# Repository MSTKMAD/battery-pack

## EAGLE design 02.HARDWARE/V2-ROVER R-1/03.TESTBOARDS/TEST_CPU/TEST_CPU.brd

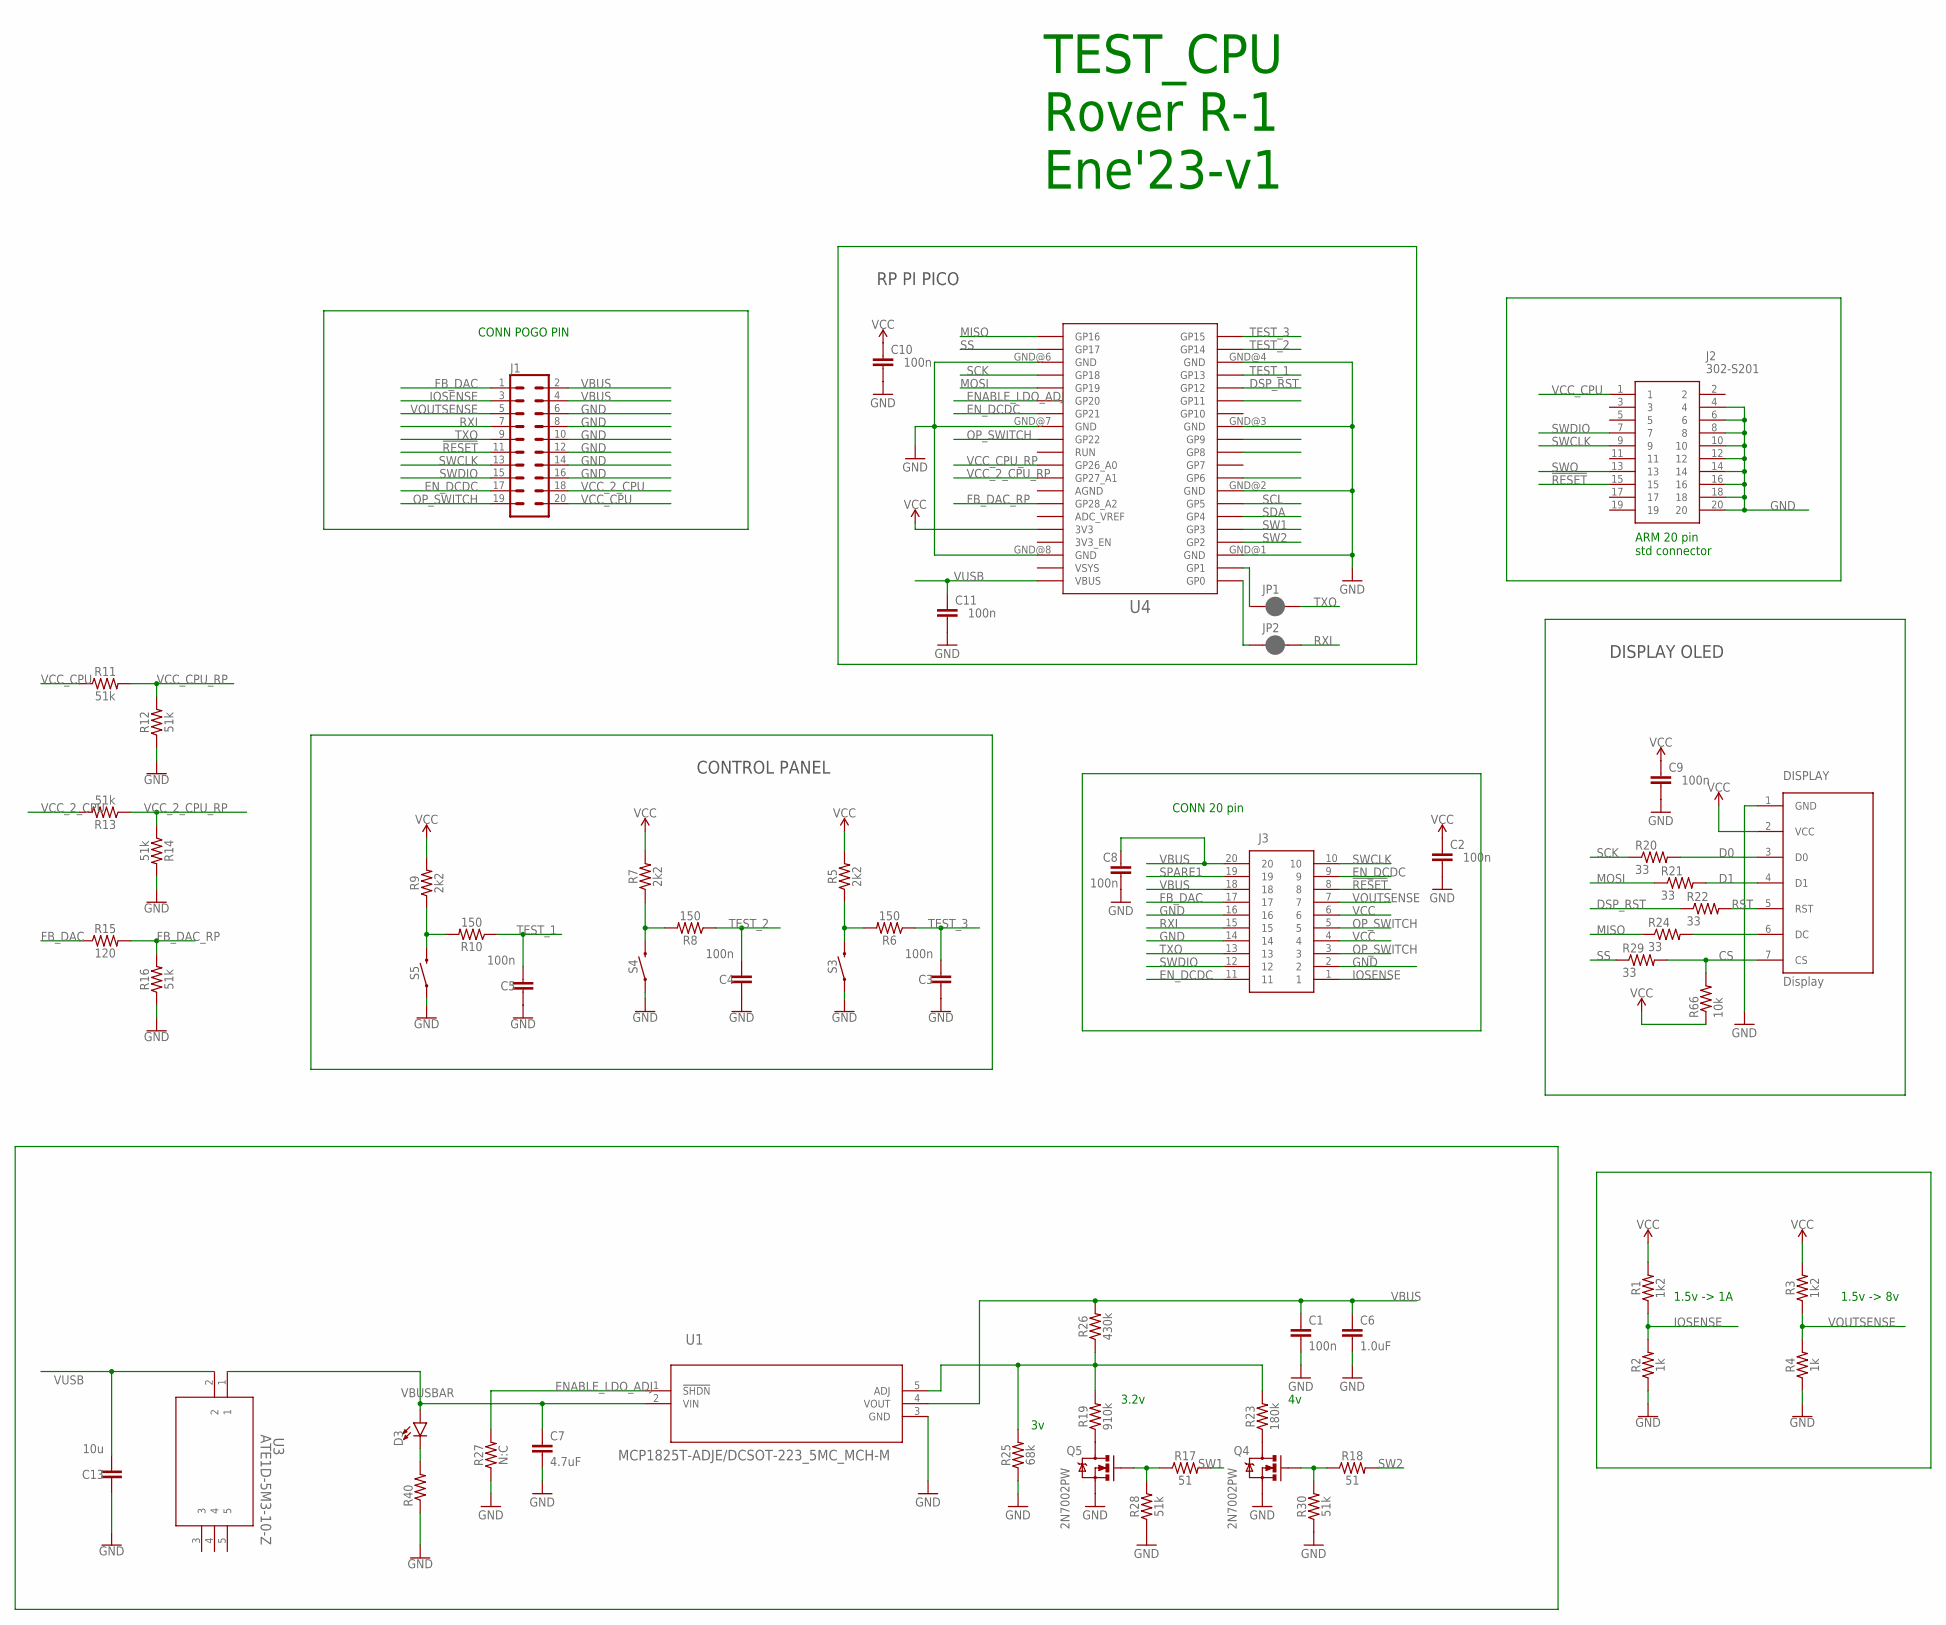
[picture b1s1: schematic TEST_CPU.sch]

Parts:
C1, C2, C3, C4, C5, C8, C9, C10, C11: 100n; 0805
C6: 1.0uF; 0805
C7: 4.7uF; 0805
C13: 10u; 0805
D3: LED3MM; LED_3MM
DISPLAY: Display; OLED_LCD
J1: CONN_10X2; 2X10
J2: 302-S201; SHDR20W66P254_2X10_3300X905X90
J3: DF40C-20DP-0.4V_51_; DF40C-20DPA
JP1, JP2: JUMPER-SMT_2_NC_PASTE_SILK; SMT-JUMPER_2_NC_PASTE_SILK
Q4, Q5: 2N7002PW; SOT323
R1, R3: 1k2; 0805
R2, R4: 1k; 0805
R5, R7, R9: 2k2; 0805
R6, R8, R10: 150; 0805
R11, R12, R13, R14, R16, R28, R30: 51k; 0805
R15: 120; 0805
R17, R18: 51; 0805
R19: 910k; 0805
R20, R21, R22, R24, R29: 33; 0805
R23: 180k; 0805
R25: 68k; 0805
R26: 430k; 0805
R27: N:C; 0805
R40: 360; 0805
R66: 10k; 0805
S3, S4, S5: MOMENTARY-SWITCH-SPST-SMD-5.2MM; TACTILE_SWITCH_SMD_5.2MM
U1: MCP1825T-ADJE/DCSOT-223_5MC_MCH-M; SOT-223_5MC_MCH-M
U3: ATE1D-5M3-10-Z; SPDT05_ATE1D_9P5X8_NDC
U4: RPI_PICO_IG-TH; RPI_PICO_TH

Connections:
!RESET: J1.11, J2.15, J3.8
CS: DISPLAY.7 (CS), R29.2, R66.2
D0: DISPLAY.3 (D0), R20.2
D1: DISPLAY.4 (D1), R21.2
DSP_RST: R22.1, U4.GP12
ENABLE_LDO_ADJ: R27.2, U1.1 (!SHDN), U4.GP20
EN_DCDC: J1.17, J3.9, J3.11, U4.GP21
FB_DAC: J1.1, J3.17, R15.1
FB_DAC_RP: R15.2, R16.2, U4.GP28_A2
GND: C1.2, C2.2, C3.1, C4.1, C5.1, C6.2, C7.2, C8.2, C9.2, C10.2, C11.2, C13.1, DISPLAY.1 (GND), J1.6, J1.8, J1.10, J1.12, J1.14, J1.16, J2.4, J2.6, J2.8, J2.10, J2.12, J2.14, J2.16, J2.18, J2.20, J3.2, J3.14, J3.16, Q4.2 (S), Q5.2 (S), R2.1, R4.1, R12.1, R14.2, R16.1, R25.1, R27.1, R28.1, R30.1, R40.1, S3.1, S4.1, S5.1, U1.3 (GND), U4.GND@1 (GND), U4.GND@2 (GND), U4.GND@3 (GND), U4.GND@4 (GND), U4.GND@6 (GND), U4.GND@7 (GND), U4.GND@8 (GND)
IOSENSE: J1.3, J3.1, R1.1, R2.2
MISO: R24.1, U4.GP16
MOSI: R21.1, U4.GP19
unnamed: R5.1, R6.2, S3.3 (2)
unnamed: R7.1, R8.2, S4.3 (2)
unnamed: JP1.1, U4.GP1
unnamed: R9.1, R10.2, S5.3 (2)
unnamed: JP2.1, U4.GP0
unnamed: DISPLAY.6 (DC), R24.2
unnamed: R19.2, R23.2, R25.2, R26.1, U1.5 (ADJ)
unnamed: Q5.1 (G), R17.1, R28.2
unnamed: D3.K (C), R40.2
unnamed: Q5.3 (D), R19.1
unnamed: Q4.1 (G), R18.1, R30.2
unnamed: Q4.3 (D), R23.1
OP_SWITCH: J1.19, J3.3, J3.5, U4.GP22
RST: DISPLAY.5 (RST), R22.2
RXI: J1.7, J3.15, JP2.2
SCK: R20.1, U4.GP18
SCL: U4.GP5
SDA: U4.GP4
SPARE1: J3.19
SS: R29.1, U4.GP17
SW1: R17.2, U4.GP3
SW2: R18.2, U4.GP2
SWCLK: J1.13, J2.9, J3.10
SWDIO: J1.15, J2.7, J3.12
SWO: J2.13
TEST_1: C5.2, R10.1, U4.GP13
TEST_2: C4.2, R8.1, U4.GP14
TEST_3: C3.2, R6.1, U4.GP15
TXO: J1.9, J3.13, JP1.2
VBUS: C1.1, C6.1, C8.1, J1.2, J1.4, J3.18, J3.20, R26.2, U1.4 (VOUT)
VBUSBAR: C7.1, D3.A, U1.2 (VIN), U3.1
VCC: C2.1, C9.1, C10.1, DISPLAY.2 (VCC), J3.4, J3.6, R1.2, R3.2, R5.2, R7.2, R9.2, R66.1, U4.3V3
VCC_2_CPU: J1.18, R13.2
VCC_2_CPU_RP: R13.1, R14.1, U4.GP27_A1
VCC_CPU: J1.20, J2.1, R11.1
VCC_CPU_RP: R11.2, R12.2, U4.GP26_A0
VOUTSENSE: J1.5, J3.7, R3.1, R4.2
VUSB: C11.1, C13.2, U3.2, U4.VBUS

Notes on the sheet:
TEST_CPU Rover R-1 Ene'23-v1
CONTROL PANEL
DISPLAY OLED
RP PI PICO
ARM 20 pin std connector
CONN 20 pin
CONN POGO PIN
1.5v -> 1A
1.5v -> 8v
3.2v

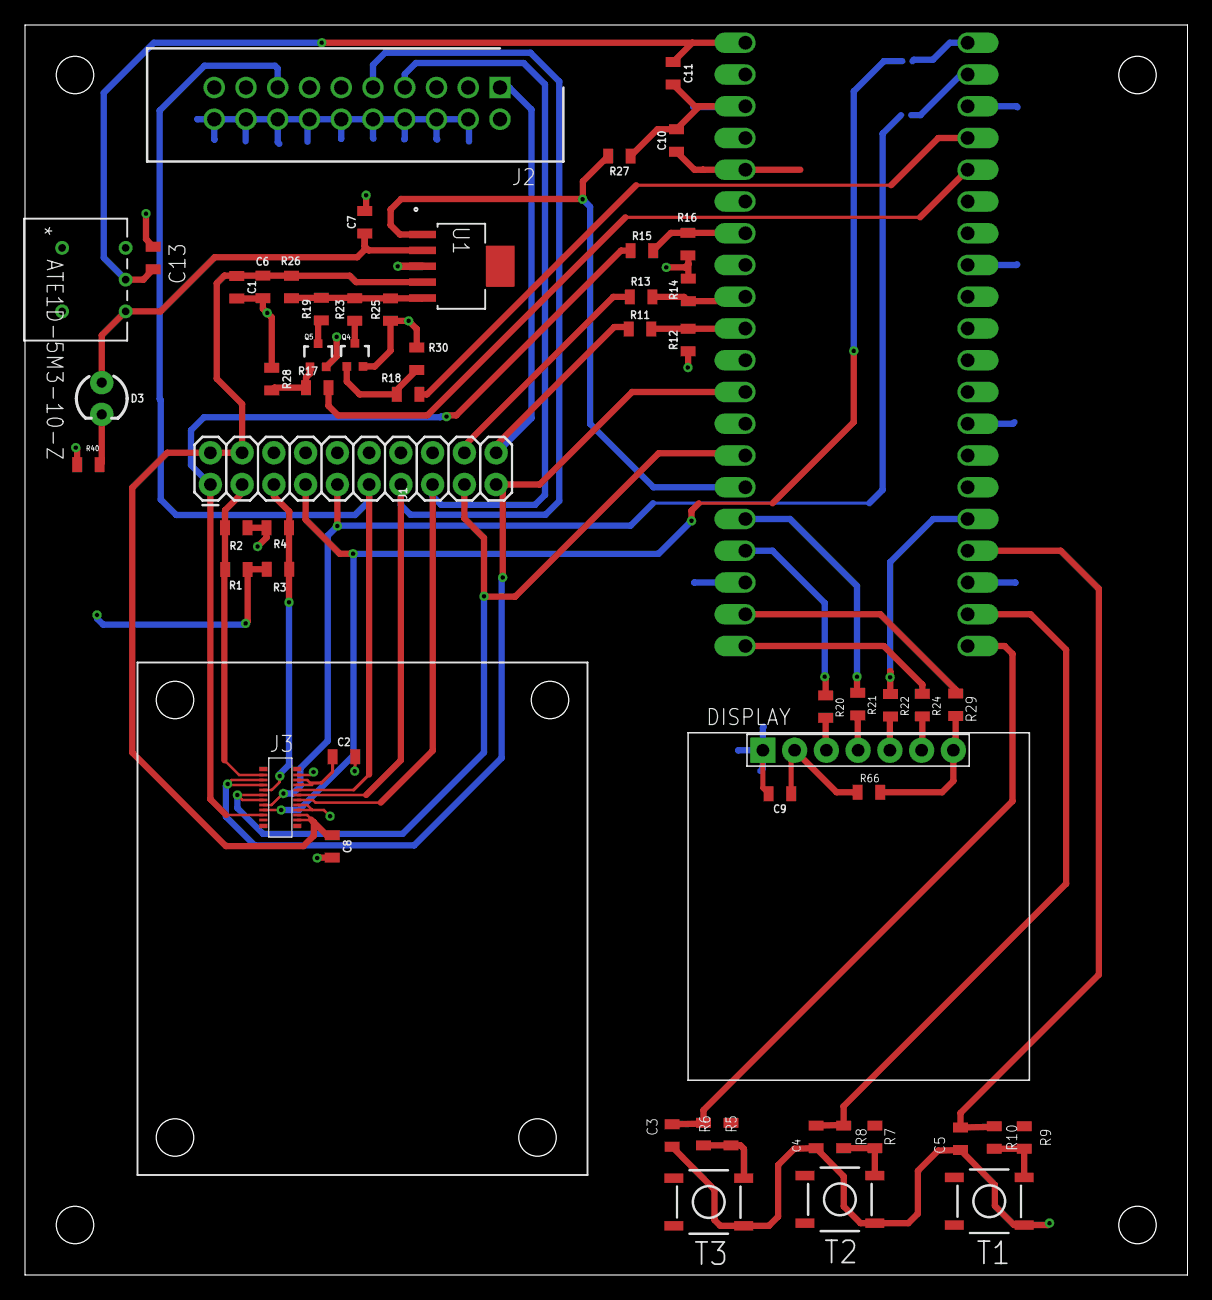
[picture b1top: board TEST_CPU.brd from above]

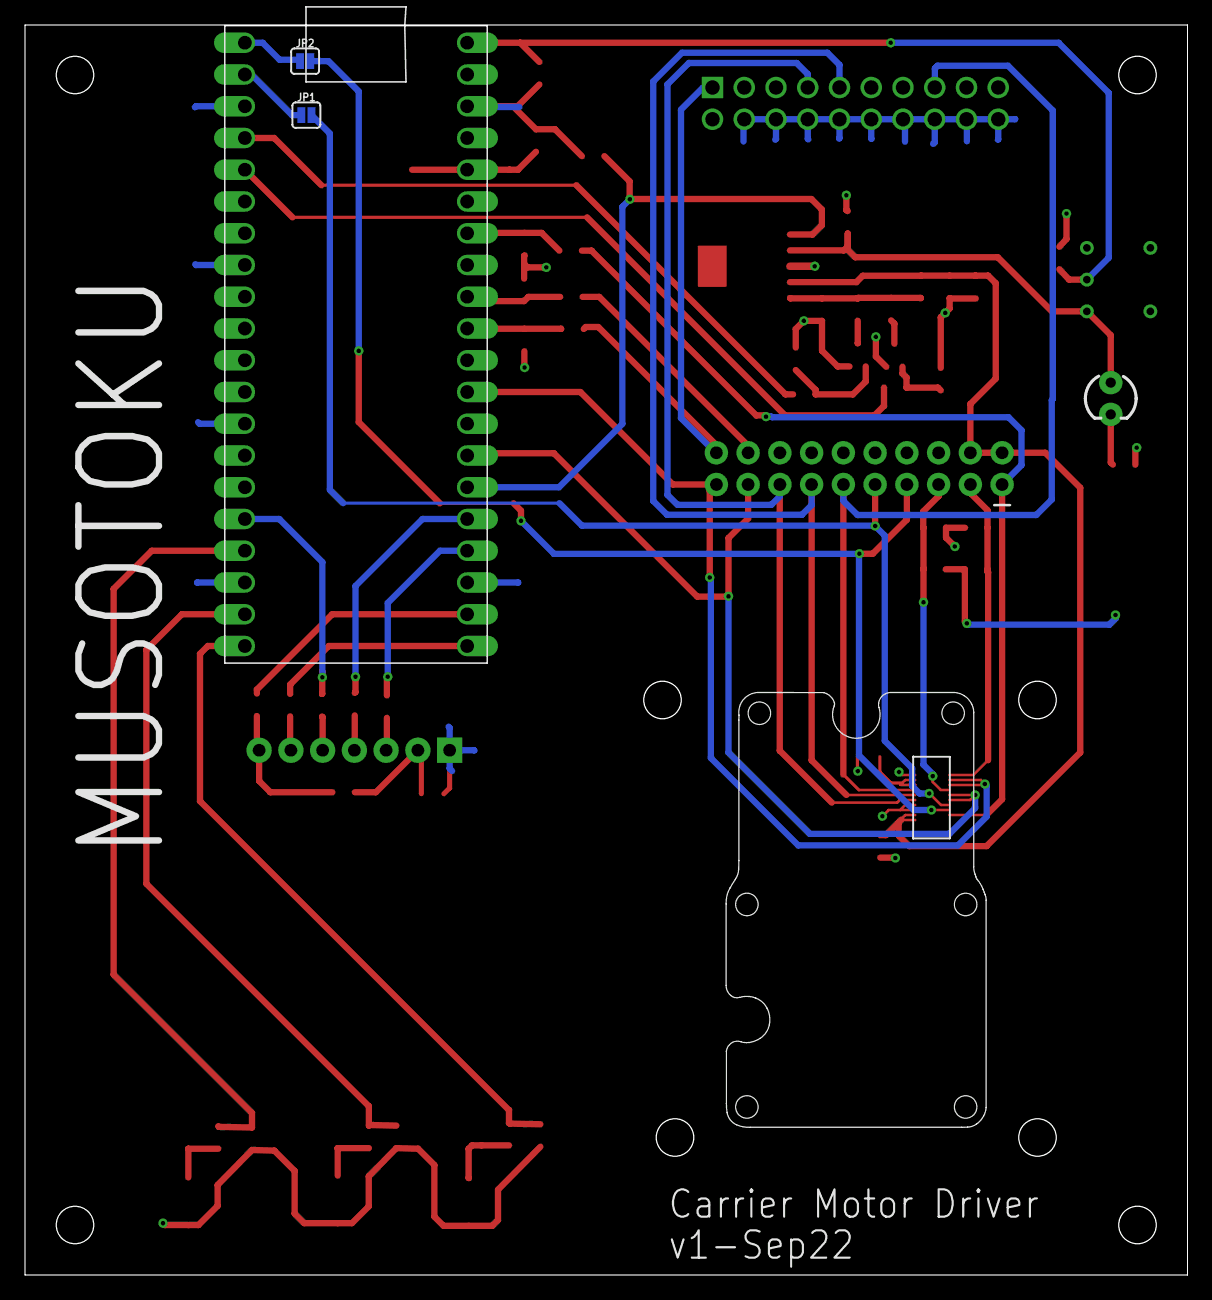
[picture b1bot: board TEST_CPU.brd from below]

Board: 2 copper layers, 93.0 x 100.0 mm, 59 parts (3 on the bottom side), 47 nets.

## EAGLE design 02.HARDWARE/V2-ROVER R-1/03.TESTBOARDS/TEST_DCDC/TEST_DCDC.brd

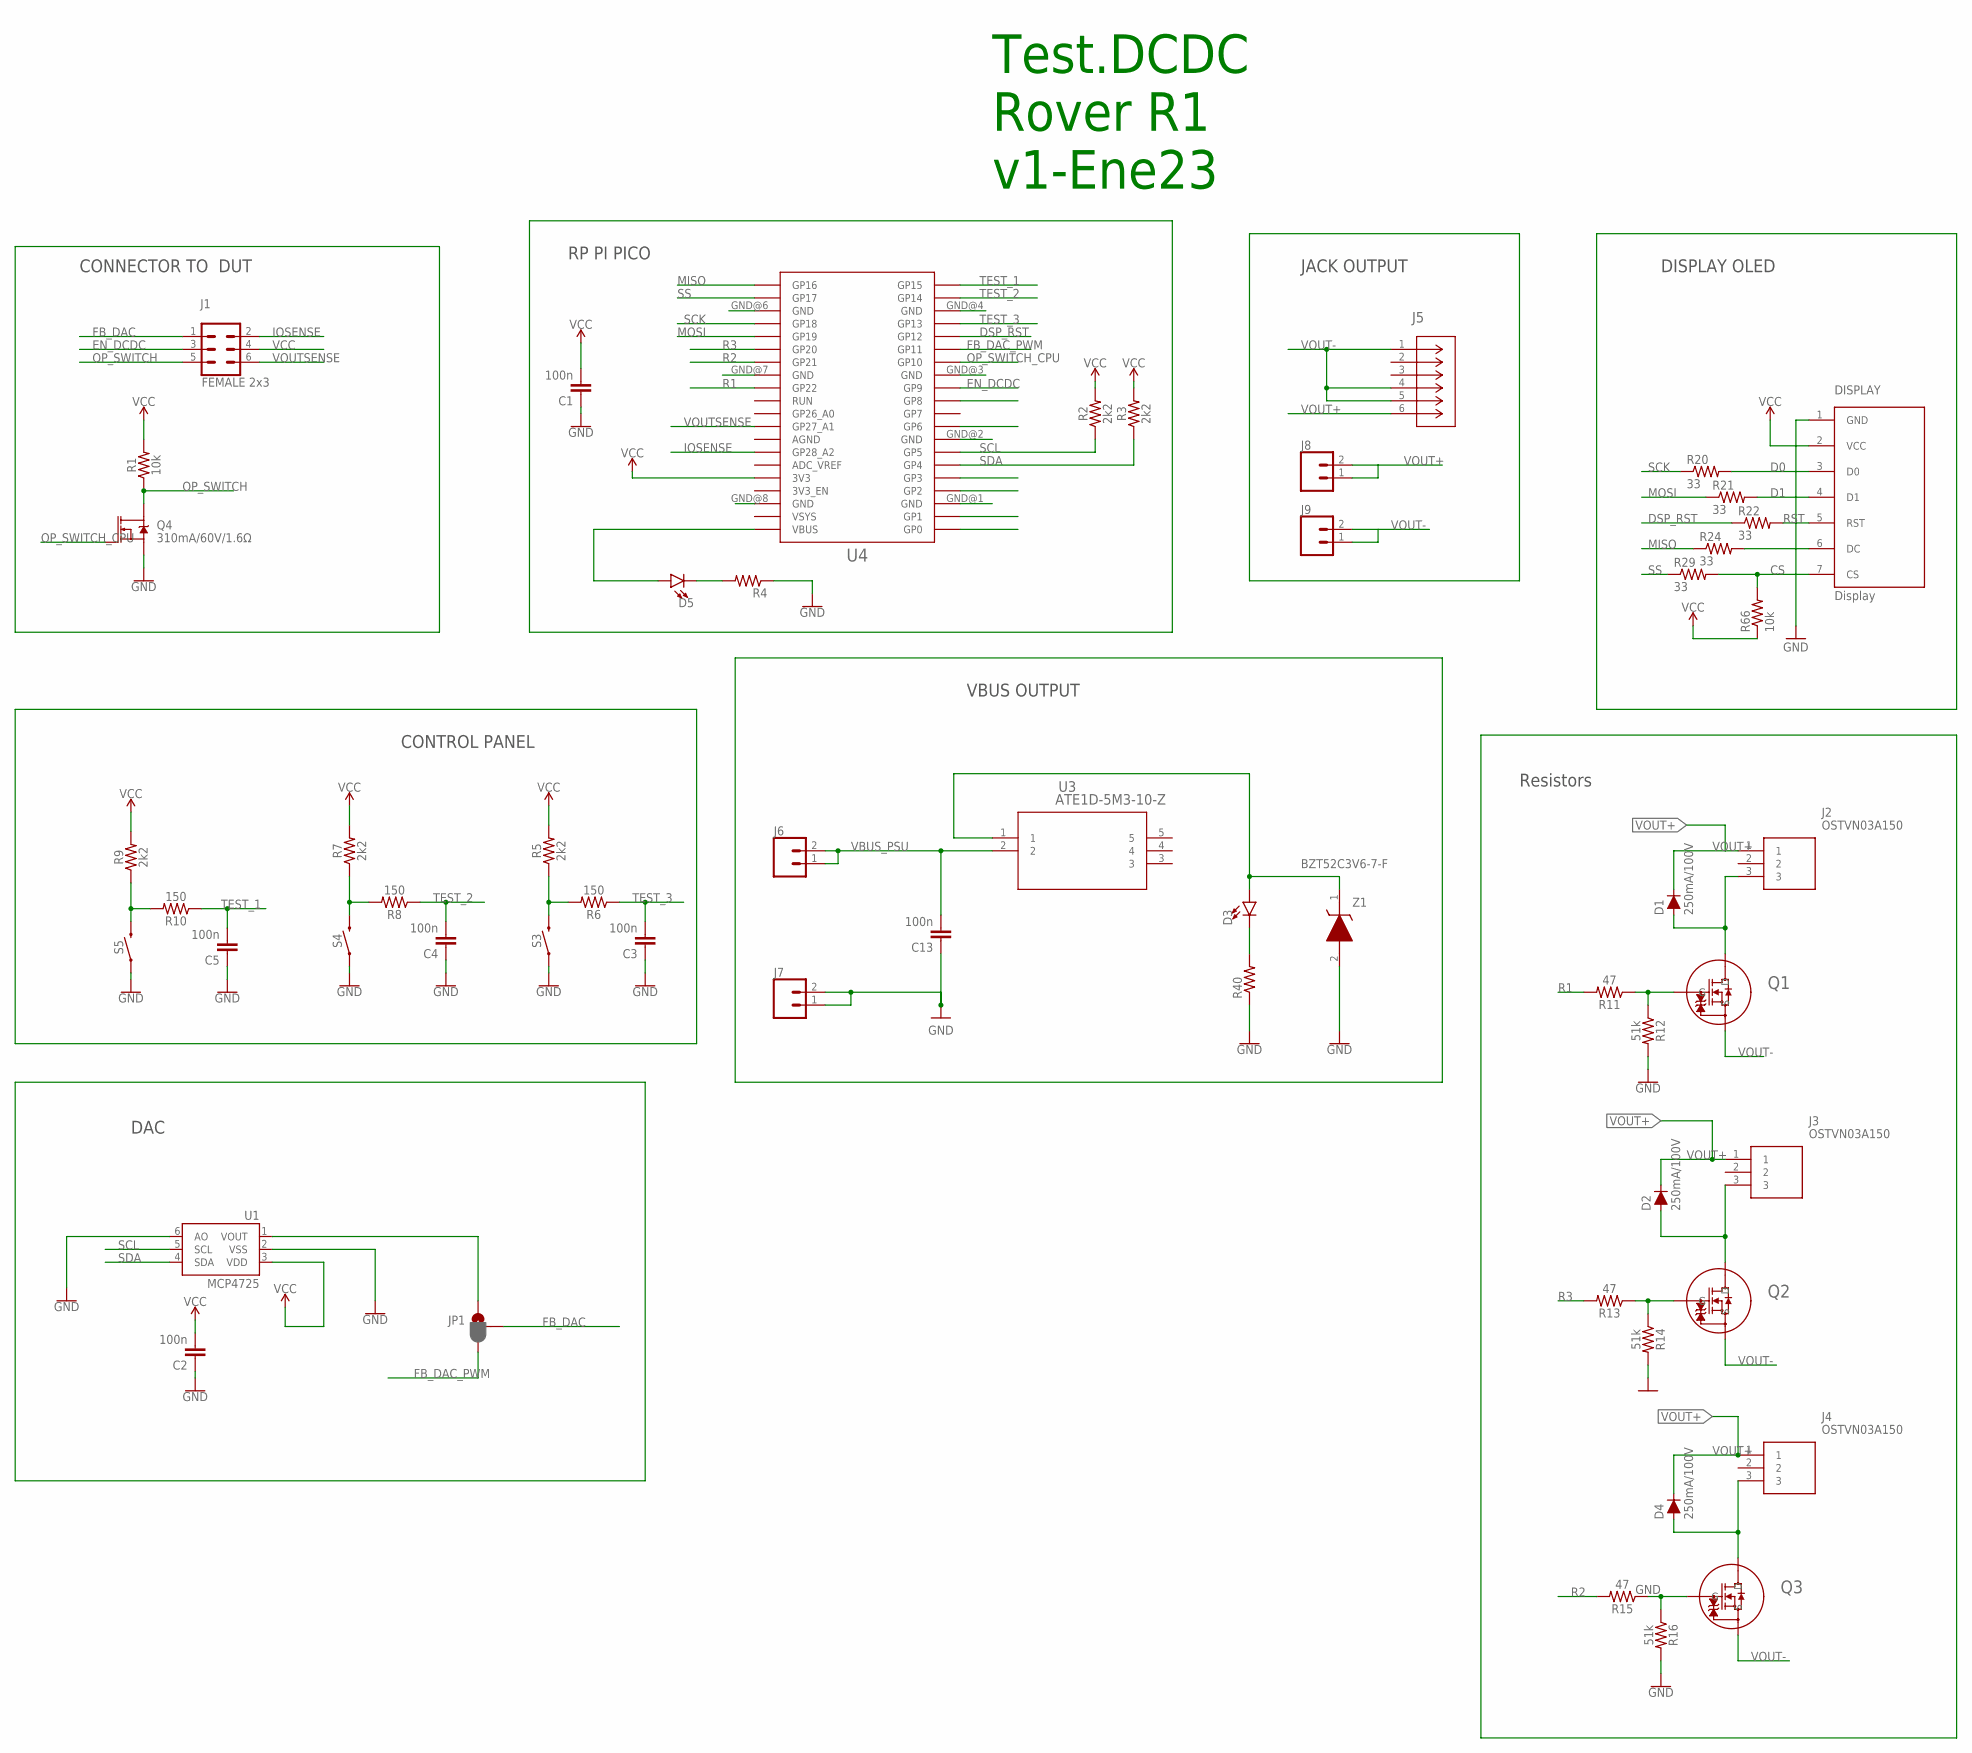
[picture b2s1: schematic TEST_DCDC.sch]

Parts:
C1, C2, C3, C4, C5, C13: 100n; C0805
D1, D2, D4: 250mA/100V; SOD-323
D3, D5: LED3MM; LED_3MM
DISPLAY: Display; OLED_LCD
J1: FEMALE 2x3; 2X3
J2, J3, J4: OSTVN03A150
J5: ACJS-MHDR; CONN_MHDR_AMP
J6, J7, J8, J9: CONN_02; 1X02
JP1: JUMPER-SMT_3_1-NC_PASTE_SILK; SMT-JUMPER_3_1-NC_PASTE_SILK
Q1, Q2, Q3: PJA3416AE_R1_00001; SOT23_PJA3416_PNJ
Q4: 310mA/60V/1.6Ω; SOT323
R1, R66: 10k; 0805
R2, R3, R5, R7, R9: 2k2; 0805
R4, R40: 360; 0805
R6, R8, R10: 150; 0805
R11, R13, R15: 47; 0805
R12, R14, R16: 51k; 0805
R20, R21, R22, R24, R29: 33; 0805
S3, S4, S5: MOMENTARY-SWITCH-SPST-SMD-5.2MM; TACTILE_SWITCH_SMD_5.2MM
U1: MCP4725; SOT23-6
U3: ATE1D-5M3-10-Z; SPDT05_ATE1D_9P5X8_NDC
U4: RPI_PICO_IG-TH; RPI_PICO_TH
Z1: BZT52C3V6-7-F; SOD3716X135N

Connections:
CS: DISPLAY.7 (CS), R29.2, R66.2
D0: DISPLAY.3 (D0), R20.2
D1: DISPLAY.4 (D1), R21.2
DSP_RST: R22.1, U4.GP12
EN_DCDC: J1.3, U4.GP9
FB_DAC: J1.1, JP1.2
FB_DAC_PWM: JP1.3, U4.GP11
GND: C1.1, C2.1, C3.1, C4.1, C5.1, C13.1, DISPLAY.1 (GND), J7.1, J7.2, Q4.2 (S), R4.1, R12.2, R14.2, R16.2, R40.1, S3.1, S4.1, S5.1, U1.2 (VSS), U1.6 (AO), U4.GND@1 (GND), U4.GND@2 (GND), U4.GND@3 (GND), U4.GND@4 (GND), U4.GND@6 (GND), U4.GND@7 (GND), U4.GND@8 (GND), Z1.2 (A)
IOSENSE: J1.2, U4.GP28_A2
MISO: R24.1, U4.GP16
MOSI: R21.1, U4.GP19
unnamed: D4.A, J4.3, Q3.3 (D)
unnamed: D2.A, J3.3, Q2.3 (D)
unnamed: R5.1, R6.2, S3.3 (2)
unnamed: R7.1, R8.2, S4.3 (2)
unnamed: R9.1, R10.2, S5.3 (2)
unnamed: DISPLAY.6 (DC), R24.2
unnamed: JP1.1, U1.1 (VOUT)
unnamed: Q1.1 (G), R11.1, R12.1
unnamed: D1.A, J2.3, Q1.3 (D)
unnamed: Q2.1 (G), R13.1, R14.1
unnamed: D5.K (C), R4.2
unnamed: D5.A, U4.VBUS
unnamed: D3.K (C), R40.2
unnamed: Q3.1 (G), R15.1, R16.1
OP_SWITCH: J1.5, Q4.3 (D), R1.1
OP_SWITCH_CPU: Q4.1 (G), U4.GP10
R1: R11.2, U4.GP22
R2: R15.2, U4.GP21
R3: R13.2, U4.GP20
RST: DISPLAY.5 (RST), R22.2
SCK: R20.1, U4.GP18
SCL: R2.1, U1.5 (SCL), U4.GP5
SDA: R3.1, U1.4 (SDA), U4.GP4
SS: R29.1, U4.GP17
TEST_1: C5.2, R10.1, U4.GP15
TEST_2: C4.2, R8.1, U4.GP14
TEST_3: C3.2, R6.1, U4.GP13
VBUS: D3.A, U3.1, Z1.1 (K)
VBUS_PSU: C13.2, J6.1, J6.2, U3.2
VCC: C1.2, C2.2, DISPLAY.2 (VCC), J1.4, R1.2, R2.2, R3.2, R5.2, R7.2, R9.2, R66.1, U1.3 (VDD), U4.3V3
VOUT+: D1.C, D2.C, D4.C, J2.1, J3.1, J4.1, J5.6, J8.1, J8.2
VOUT-: J5.1, J5.4, J5.5, J9.1, J9.2, Q1.2 (S), Q2.2 (S), Q3.2 (S)
VOUTSENSE: J1.6, U4.GP27_A1

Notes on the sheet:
Test.DCDC Rover R1 v1-Ene23
CONTROL PANEL
VBUS OUTPUT
Resistors
DISPLAY OLED
RP PI PICO
DAC
CONNECTOR TO DUT
JACK OUTPUT

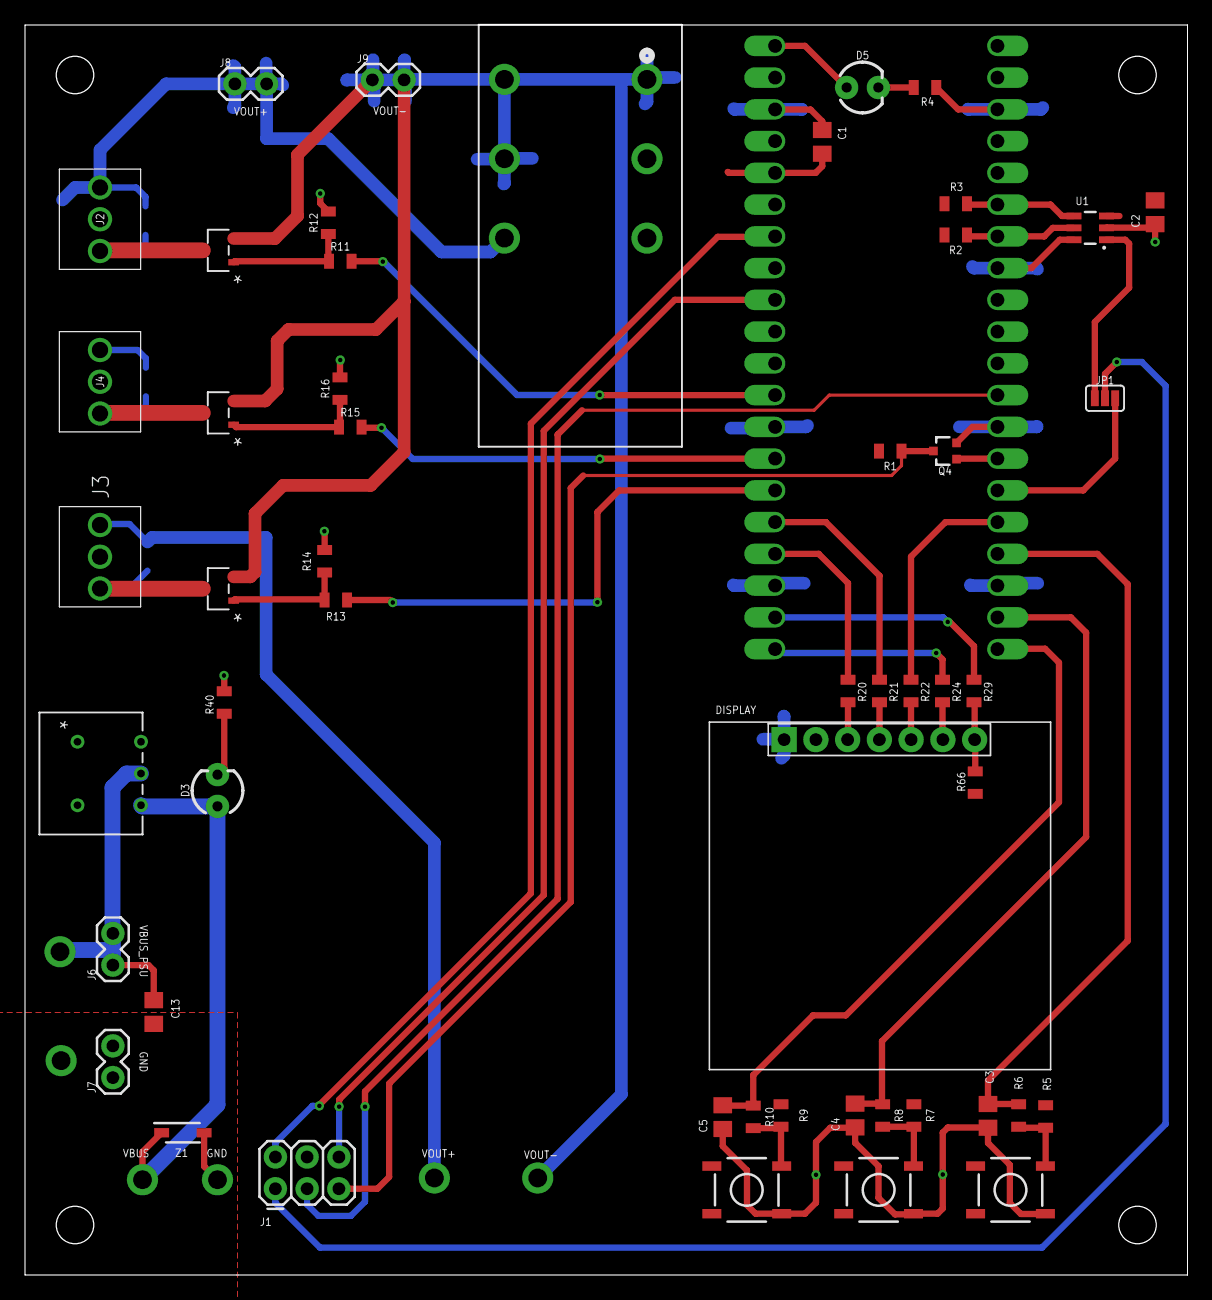
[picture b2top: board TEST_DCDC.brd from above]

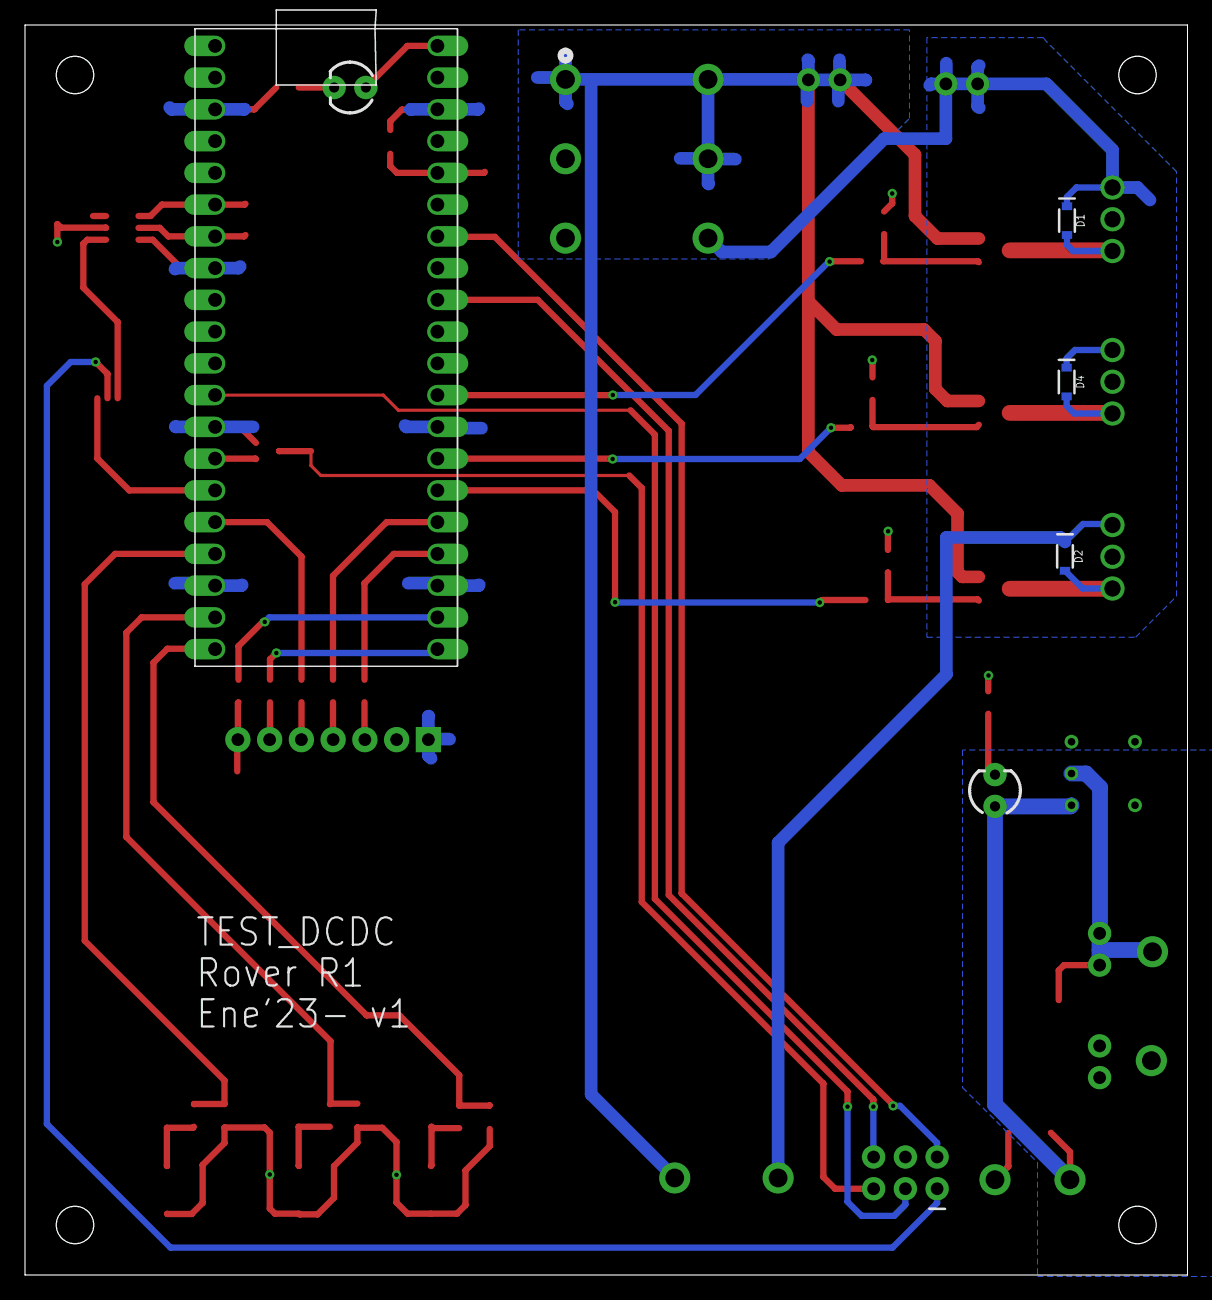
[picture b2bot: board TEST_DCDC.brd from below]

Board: 2 copper layers, 93.0 x 100.0 mm, 56 parts (4 on the bottom side), 44 nets.

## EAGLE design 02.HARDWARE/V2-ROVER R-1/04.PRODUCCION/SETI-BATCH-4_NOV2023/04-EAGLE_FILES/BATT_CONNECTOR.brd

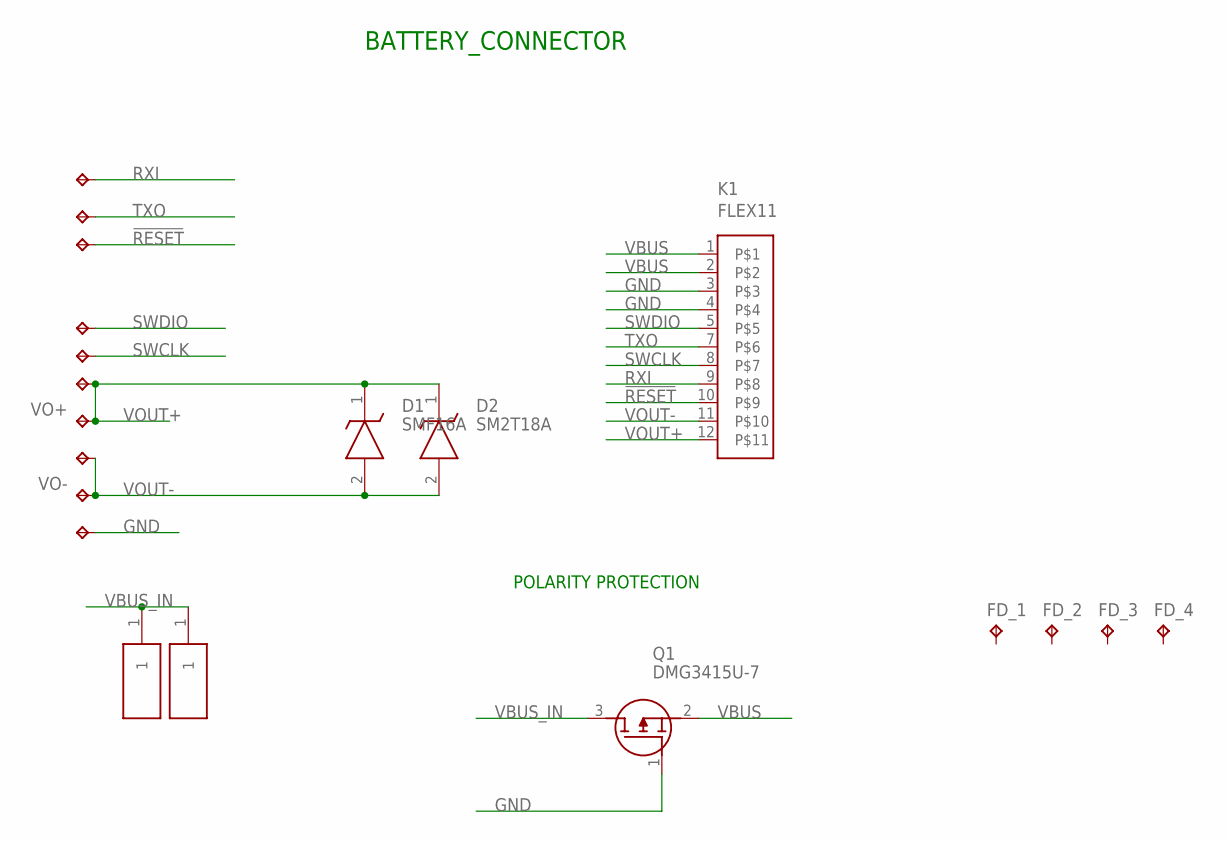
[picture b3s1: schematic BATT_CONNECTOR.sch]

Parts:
!RESET: TPB2,54; B2,54
D1: SMF16A; SODFL3618X110N
D2: SM2T18A
FD_1, FD_2, FD_3, FD_4: FD_1; TP06SQ
GND: TPB2,54; B2,54
H1, H2: S1761-42R; S176142R
K1: FLEX11
Q1: DMG3415U-7; SSM3J332RLFT
RXI: TPB2,54; B2,54
SWCLK: TPB2,54; B2,54
SWDIO: TPB2,54; B2,54
TXO: TPB2,54; B2,54
VO+: TPB2,54; B2,54
VO-: TPB2,54; B2,54
VOUT+1: TPB2,54; B2,54
VOUT-1: TPB2,54; B2,54

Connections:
!RESET: !RESET.TP, K1.10
GND: GND.TP, K1.3, K1.4, Q1.1 (G)
RXI: K1.9, RXI.TP
SWCLK: K1.8, SWCLK.TP
SWDIO: K1.5, SWDIO.TP
TXO: K1.7, TXO.TP
VBUS: K1.1, K1.2, Q1.2 (S)
VBUS_IN: H1.1, H2.1, Q1.3 (D)
VOUT+: D1.1 (K), D2.1 (K), K1.12, VO+.TP, VOUT+1.TP
VOUT-: D1.2 (A), D2.2 (A), K1.11, VO-.TP, VOUT-1.TP

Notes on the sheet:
POLARITY PROTECTION
BATTERY_CONNECTOR

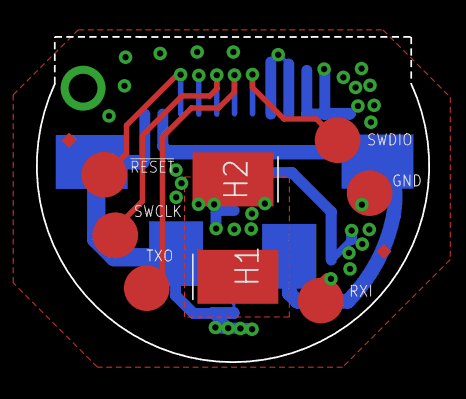
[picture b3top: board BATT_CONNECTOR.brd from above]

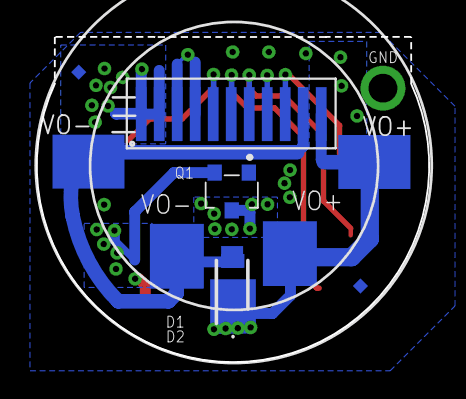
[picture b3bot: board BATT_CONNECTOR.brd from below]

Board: 4 copper layers, 21.8 x 18.1 mm, 20 parts (10 on the bottom side), 10 nets.

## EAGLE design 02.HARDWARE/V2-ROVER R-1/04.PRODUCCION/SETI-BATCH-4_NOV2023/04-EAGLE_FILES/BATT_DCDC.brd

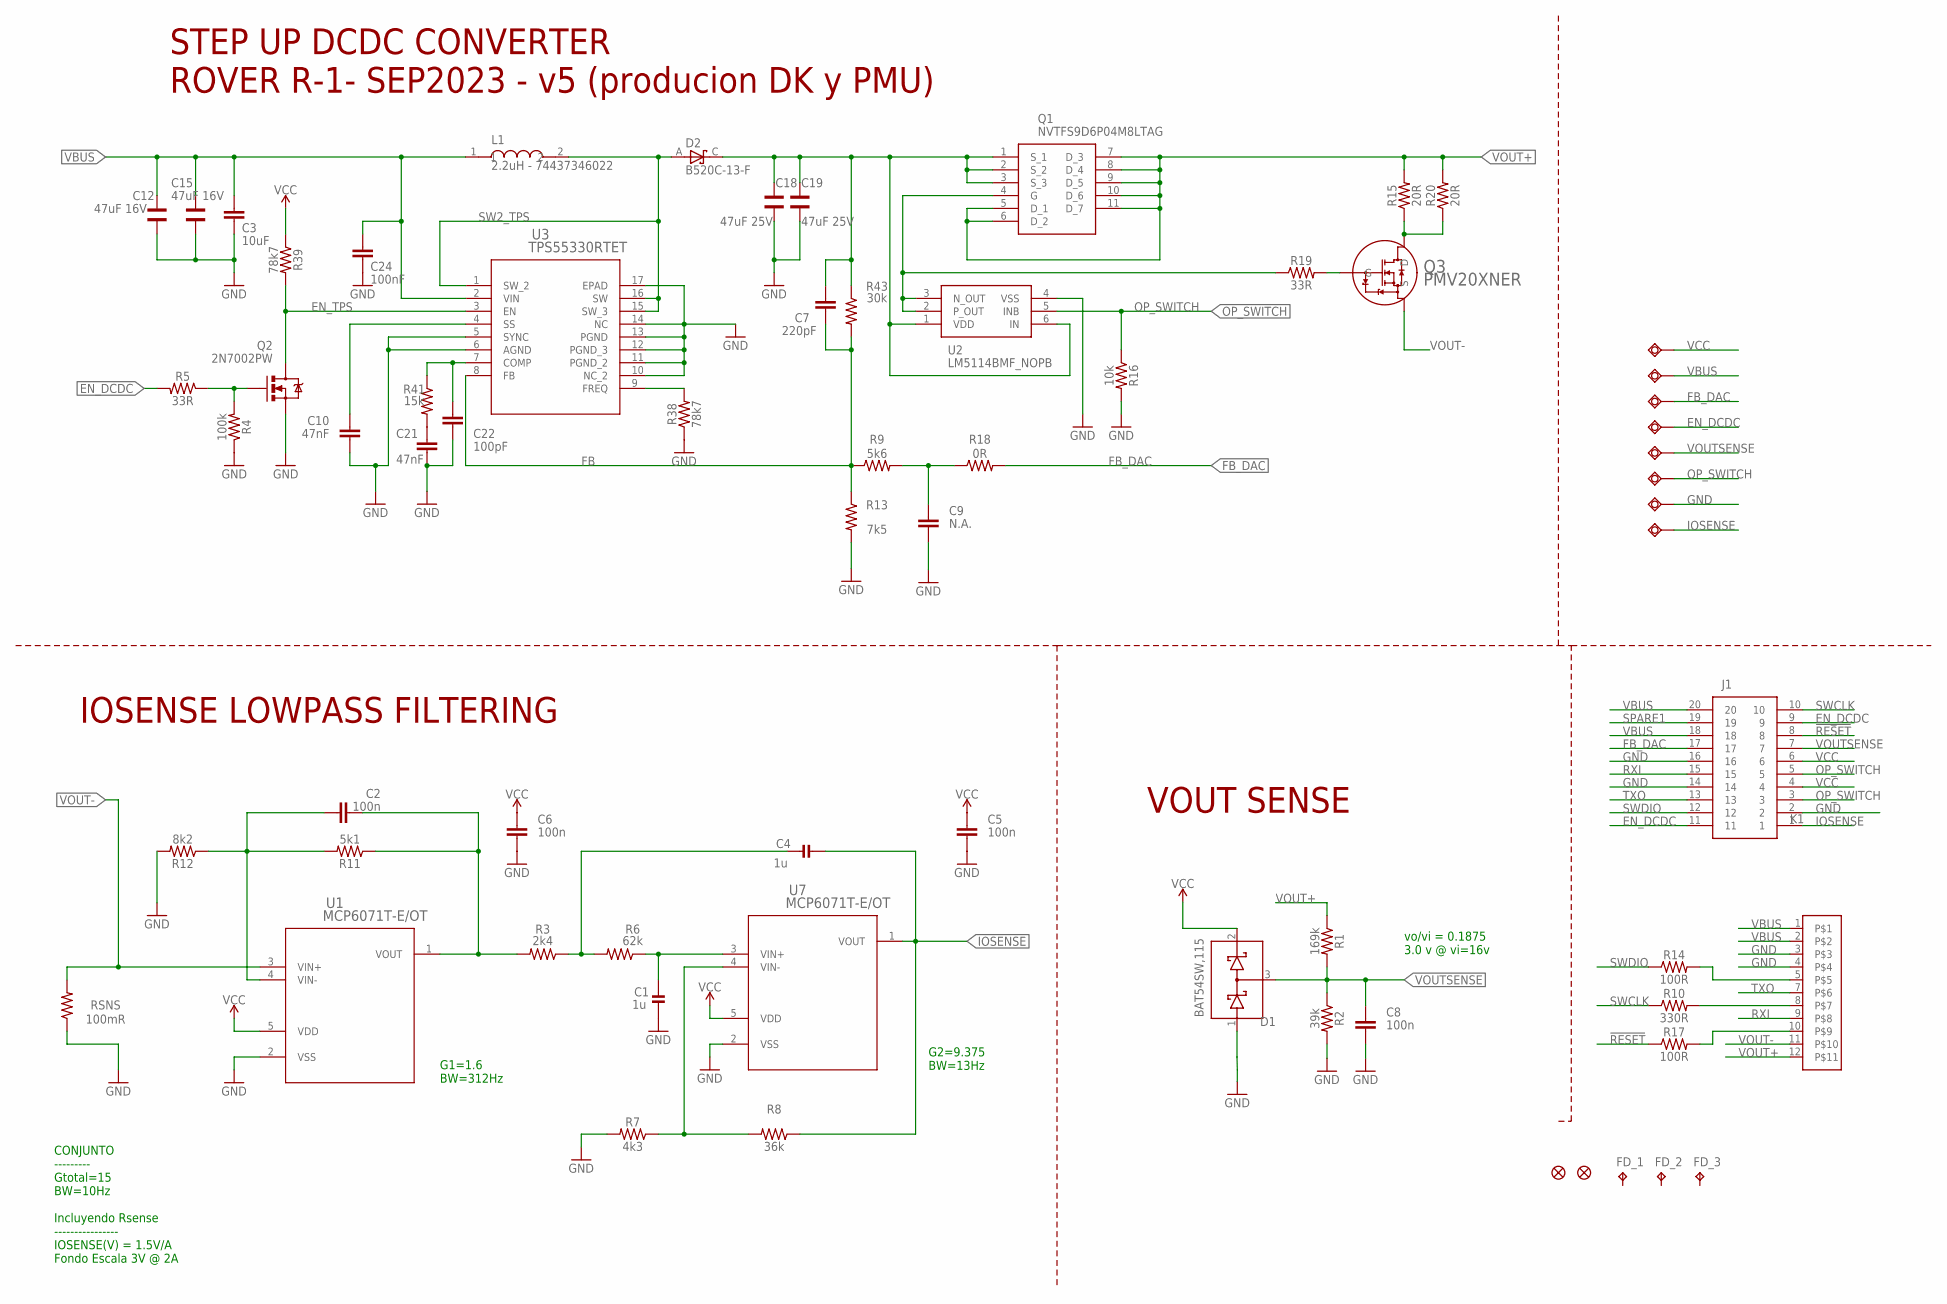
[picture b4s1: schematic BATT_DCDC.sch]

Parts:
C1, C4: 1u; 0603-NO
C2, C5, C6, C8: 100n; 0603
C3: 10uF; 0805
C7: 220pF; 0603
C9: N.A.; 0603
C10, C21: 47nF; 0603
C12, C15: 47uF 16V; WCAP-CSGP_1210
C18, C19: 47uF 25V; WCAP-CSGP_1210
C22: 100pF; 0603
C24: 100nF; 0603
D1: BAT54SW,115; SOT65P210X110-3N
D2: B520C-13-F; DIOM7959X250N
EN_DCDC: TESTPAD_TPSQB1,27; TESTPAD_B1,27
FB_DAC: TESTPAD_TPSQB1,27; TESTPAD_B1,27
FD_1, FD_2, FD_3: FD_1; TP06SQ
GND: TESTPAD_TPSQB1,27; TESTPAD_B1,27
IOSENSE: TESTPAD_TPSQB1,27; TESTPAD_B1,27
J1: DF40C-20DP-0.4V_51_; DF40C-20DPA
K1: FLEX11
L1: 2.2uH - 74437346022; INDM7366X500
OP_SWITCH: TESTPAD_TPSQB1,27; TESTPAD_B1,27
Q1: NVTFS9D6P04M8LTAG; NVTFS5124PLTWG
Q2: 2N7002PW; SOT323
Q3: PMV20XNER; SOT23-TO-236AB_NEX-L
R1: 169k; 0402
R2: 39k; 0402
R3: 2k4; 0603
R4: 100k; 0402
R5, R19: 33R; 0402
R6: 62k; 0603
R7: 4k3; 0603
R8: 36k; 0603
R9: 5k6; 0402
R10: 330R; 0402
R11: 5k1; 0402
R12: 8k2; 0402
R13: 7k5; 0402
R14, R17: 100R; 0402
R15, R20: 20R; 1206
R16: 10k; 0402
R18: 0R; 0402
R38, R39: 78k7; 0402
R41: 15k; 0402
R43: 30k; 0402
RSNS: 100mR; 1206
U1, U7: MCP6071T-E/OT; SOT-23-5_MC_MCH
U2: LM5114BMF_NOPB; SOT95P280X145-6N
U3: TPS55330RTET; RTE16_1P66X1P66_TEX
U$1, U$2: FIDUCIAL""; FIDUCIAL_1MM
VBUS: TESTPAD_TPSQB1,27; TESTPAD_B1,27
VCC: TESTPAD_TPSQB1,27; TESTPAD_B1,27
VOUTSENSE: TESTPAD_TPSQB1,27; TESTPAD_B1,27

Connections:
!RESET: J1.8, R17.1
COMP_TPS: C22.2, R41.1, U3.7 (COMP)
EN_DCDC: EN_DCDC.TP, J1.9, J1.11, R5.2
EN_TPS: Q2.3 (D), R39.2, U3.3 (EN)
FB: C7.1, R9.1, R13.1, R43.2, U3.8 (FB)
FB_DAC: FB_DAC.TP, J1.17, R18.2
FREQ_TPS: R38.2, U3.9 (FREQ)
GND: C1.2, C3.1, C5.2, C6.2, C8.2, C9.2, C10.2, C12.1, C15.1, C18.1, C19.1, C21.1, C22.1, C24.1, D1.1 (A), GND.TP, J1.2, J1.14, J1.16, K1.3, K1.4, Q2.2 (S), R2.2, R4.1, R7.2, R12.2, R13.2, R16.2, R38.1, RSNS.1, U1.2 (VSS), U2.4 (VSS), U3.5 (SYNC), U3.6 (AGND), U3.10 (NC_2), U3.11 (PGND_2), U3.12 (PGND_3), U3.13 (PGND), U3.14 (NC), U3.17 (EPAD), U7.2 (VSS)
IOSENSE: C4.2, IOSENSE.TP, J1.1, R8.1, U7.1 (VOUT)
ISENSE_RAW: C2.1, R3.2, R11.1, U1.1 (VOUT)
unnamed: C2.2, R11.2, R12.1, U1.4 (VIN-)
unnamed: R7.1, R8.2, U7.4 (VIN-)
unnamed: C4.1, R3.1, R6.2
unnamed: Q2.1 (G), R4.2, R5.1
unnamed: C1.1, R6.1, U7.3 (VIN+)
unnamed: K1.8, R10.2
unnamed: Q3.3 (D), R15.1, R20.1
unnamed: Q1.4 (G), R19.1, U2.2 (P_OUT), U2.3 (N_OUT)
unnamed: K1.10, R17.2
unnamed: K1.5, R14.2
unnamed: C9.1, R9.2, R18.1
unnamed: Q3.1 (G), R19.2
unnamed: C10.1, U3.4 (SS)
unnamed: C21.2, R41.2
OP_SWITCH: J1.3, J1.5, OP_SWITCH.TP, R16.1, U2.5 (INB)
RXI: J1.15, K1.9
SPARE1: J1.19
SW2_TPS: D2.A, L1.2, U3.1 (SW_2), U3.15 (SW_3), U3.16 (SW)
SWCLK: J1.10, R10.1
SWDIO: J1.12, R14.1
TXO: J1.13, K1.7
VBUS: C3.2, C12.2, C15.2, C24.2, J1.18, J1.20, K1.1, K1.2, L1.1, U3.2 (VIN), VBUS.TP
VCC: C5.1, C6.1, D1.2 (C), J1.4, J1.6, R39.1, U1.5 (VDD), U7.5 (VDD), VCC.TP
VOUT+: K1.12, Q1.5 (D_1), Q1.6 (D_2), Q1.7 (D_3), Q1.8 (D_4), Q1.9 (D_5), Q1.10 (D_6), Q1.11 (D_7), R1.1, R15.2, R20.2
VOUT-: K1.11, Q3.2 (S), RSNS.2, U1.3 (VIN+)
VOUTSENSE: C8.1, D1.3 (A-C), J1.7, R1.2, R2.1, VOUTSENSE.TP
VSOURCE: C7.2, C18.2, C19.2, D2.C, Q1.1 (S_1), Q1.2 (S_2), Q1.3 (S_3), R43.1, U2.1 (VDD), U2.6 (IN)

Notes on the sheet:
vo/vi = 0.1875 3.0 v @ vi=16v
VOUT SENSE
G2=9.375 BW=13Hz
IOSENSE LOWPASS FILTERING
STEP UP DCDC CONVERTER ROVER R-1- SEP2023 - v5 (producion DK y PMU)
G1=1.6 BW=312Hz
CONJUNTO --------- Gtotal=15 BW=10Hz Incluyendo Rsense ---------------- IOSENSE(V) = 1.5V/A Fondo Escala 3V @ 2A

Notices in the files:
parts and their libraries:
SparkFun-Switches: Licensing: Creative Commons ShareAlike 4.0 International - https://creativecommons.org/licenses/by-sa/4.0
COPYRIGHT: Copyright (C) 2022 Ultra Librarian. All rights reserved.
COPYRIGHT: Copyright (C) 2018 Accelerated Designs. All rights reserved
